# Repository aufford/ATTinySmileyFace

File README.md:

# ATTinySmileyFace
** In Development **
The idea of this project is to develop a cheap microcontroller project for students. 

# PCB Design
The Kicad Project file is provided here in its entirety. You can get three of the boards fabbed up by OSHPark for $20 (as of Feb 2025), then solder the components in yourself. (Future work to reduce the price point).

# Arduino Code
You can find a basic Arduino sketch here. The idea is for the kids to make the smiley face eyes flash in whatever pattern they want.

# Simulation
You can open the simulation project at https://wokwi.com/projects/422974727593661441
The students can practice with different code to make the eyes blink, wink, etc. Once they have a pattern they like, we can program their ATTiny and then load it onto their board.

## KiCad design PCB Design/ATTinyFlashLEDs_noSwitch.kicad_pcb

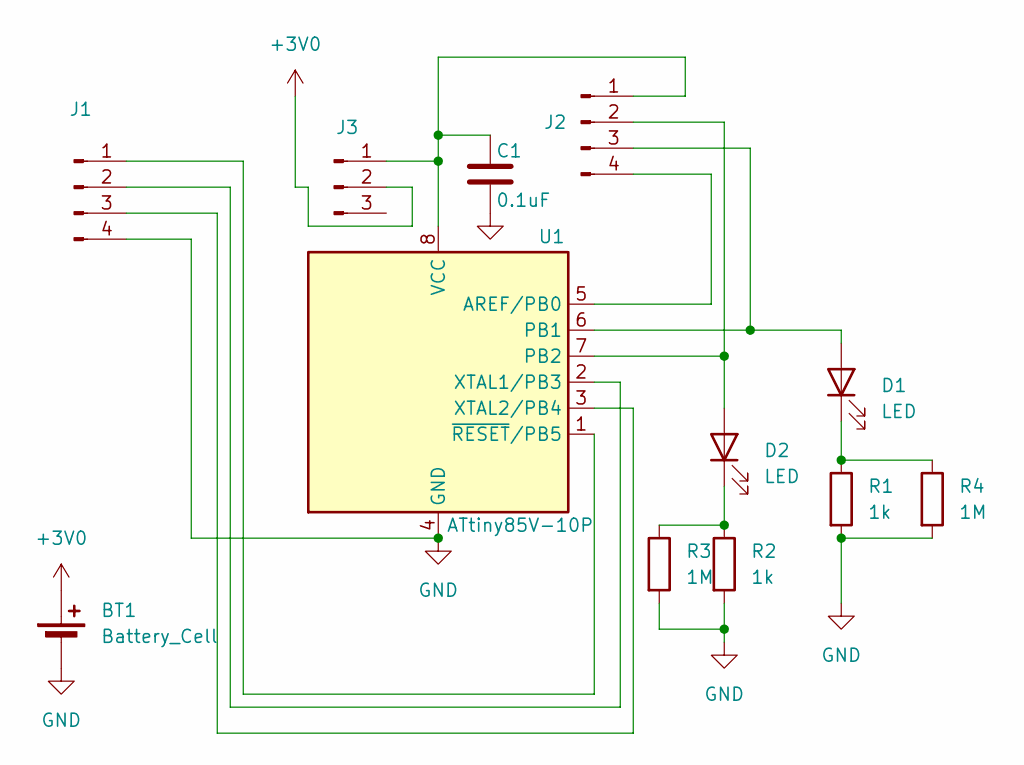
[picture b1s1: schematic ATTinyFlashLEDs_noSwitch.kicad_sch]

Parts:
BT1: Battery_Cell; BatteryHolder_Keystone_3034_1x20mm
C1: 0.1uF; C_0603_1608Metric_Pad1.08x0.95mm_HandSolder
D1, D2: LED; LED_D3.0mm
J1, J2: Conn_01x04_Pin; PinHeader_1x04_P2.54mm_Vertical
J3: Conn_01x03_Pin; PinHeader_1x03_P2.54mm_Vertical
R1, R2: 1k; R_0603_1608Metric_Pad0.98x0.95mm_HandSolder
R3, R4: 1M; R_Axial_DIN0309_L9.0mm_D3.2mm_P12.70mm_Horizontal
U1: ATtiny85V-10P; DIP-8_W7.62mm

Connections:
+3V0: BT1.1 (+), J3.2
GND: BT1.2 (-), C1.2, J1.4, R1.2, R2.2, R3.2, R4.2, U1.4 (GND)
unnamed: D1.2 (A), J2.3, U1.6 (PB1)
unnamed: D1.1 (K), R1.1, R4.1
unnamed: D2.2 (A), J2.2, U1.7 (PB2)
unnamed: D2.1 (K), R2.1, R3.1
unnamed: J1.1, U1.1 (~RESET/PB5)
unnamed: J1.2, U1.2 (XTAL1/PB3)
unnamed: J1.3, U1.3 (XTAL2/PB4)
unnamed: C1.1, J2.1, J3.1, U1.8 (VCC)
unnamed: J2.4, U1.5 (AREF/PB0)

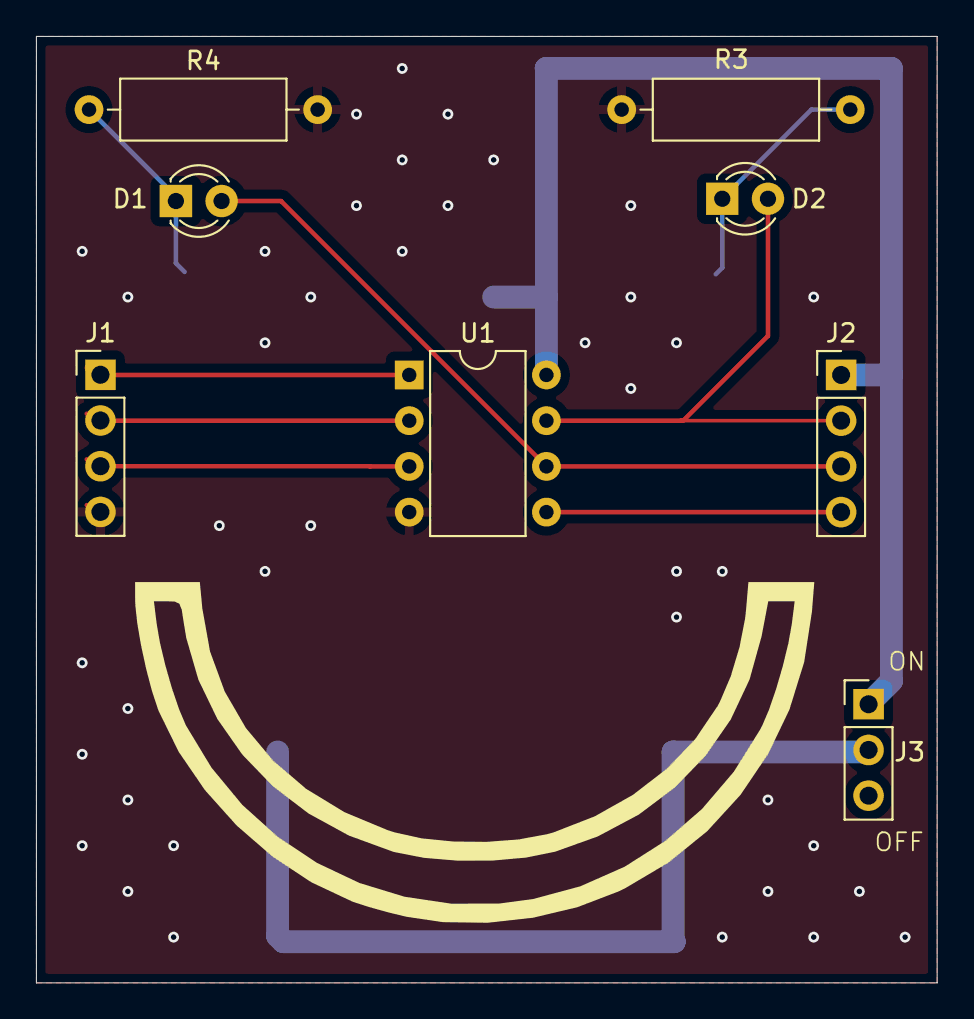
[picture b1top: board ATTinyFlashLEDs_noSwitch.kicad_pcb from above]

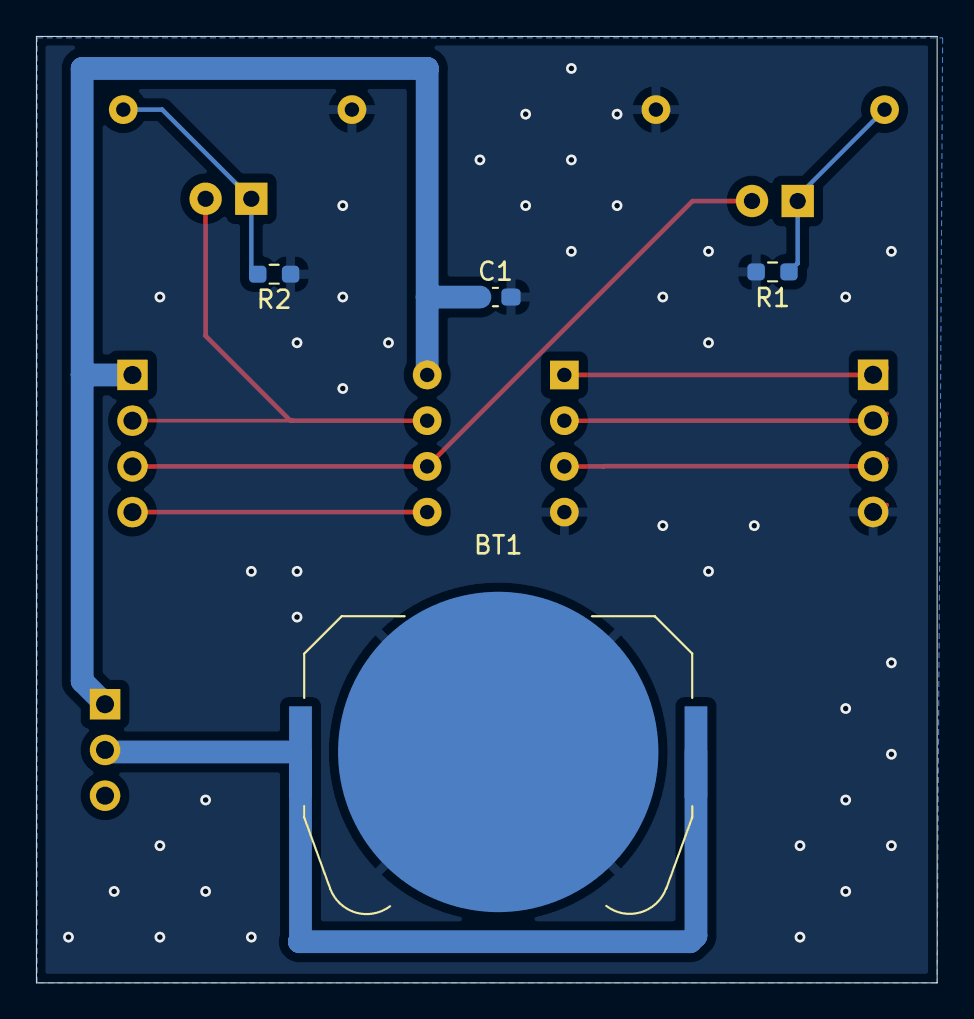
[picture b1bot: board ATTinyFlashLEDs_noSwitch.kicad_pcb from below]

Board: 2 copper layers, 50.0 x 52.6 mm, 12 parts (4 on the bottom side), 11 nets.

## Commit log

2025-02-15 Update with Folder Structure
2025-02-15 Update README.md
    Update readme
2025-02-15 Add image to README.md
    Added PWA image
2025-02-19 Updates with front pour and stitching vias
2025-02-25 Added decoupling capacitor, moved power trace to back copper
2025-02-25 Updated pour and stitching vias
2025-02-25 Update README.md
    Updated with new board image
